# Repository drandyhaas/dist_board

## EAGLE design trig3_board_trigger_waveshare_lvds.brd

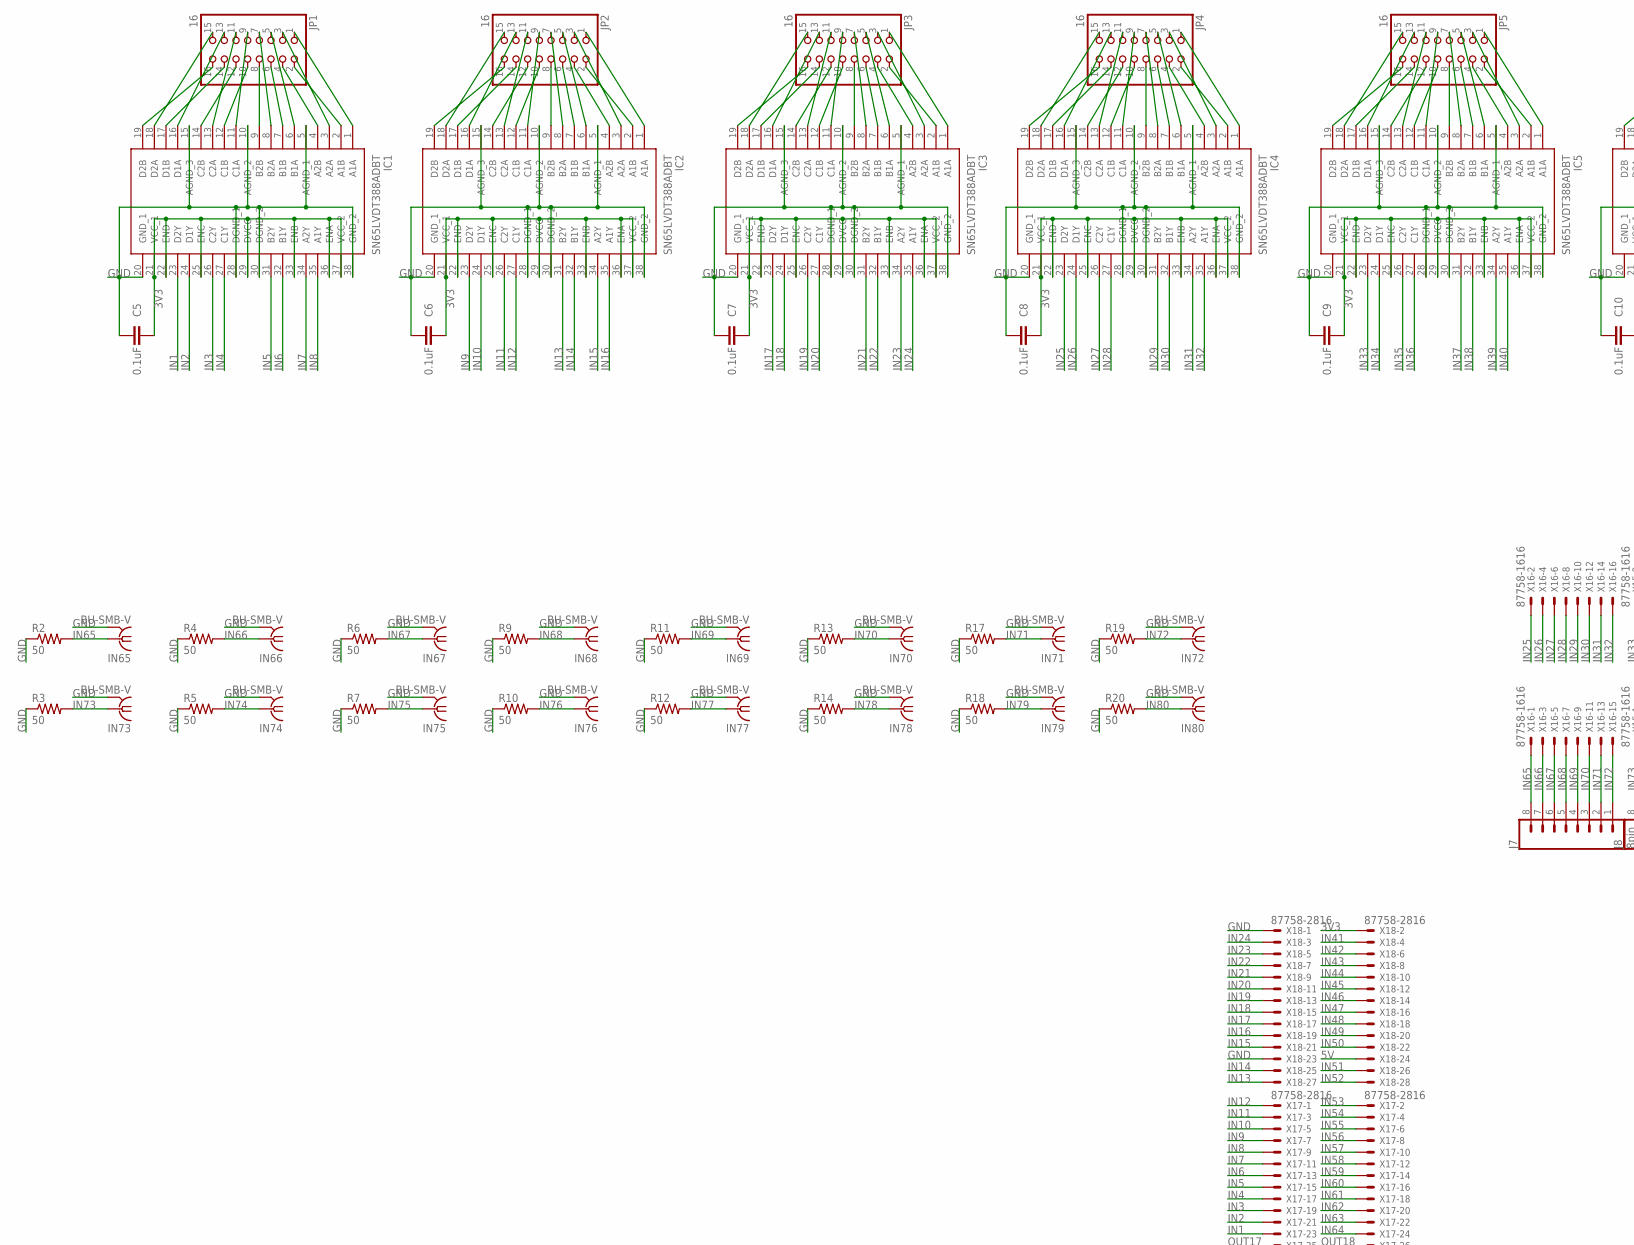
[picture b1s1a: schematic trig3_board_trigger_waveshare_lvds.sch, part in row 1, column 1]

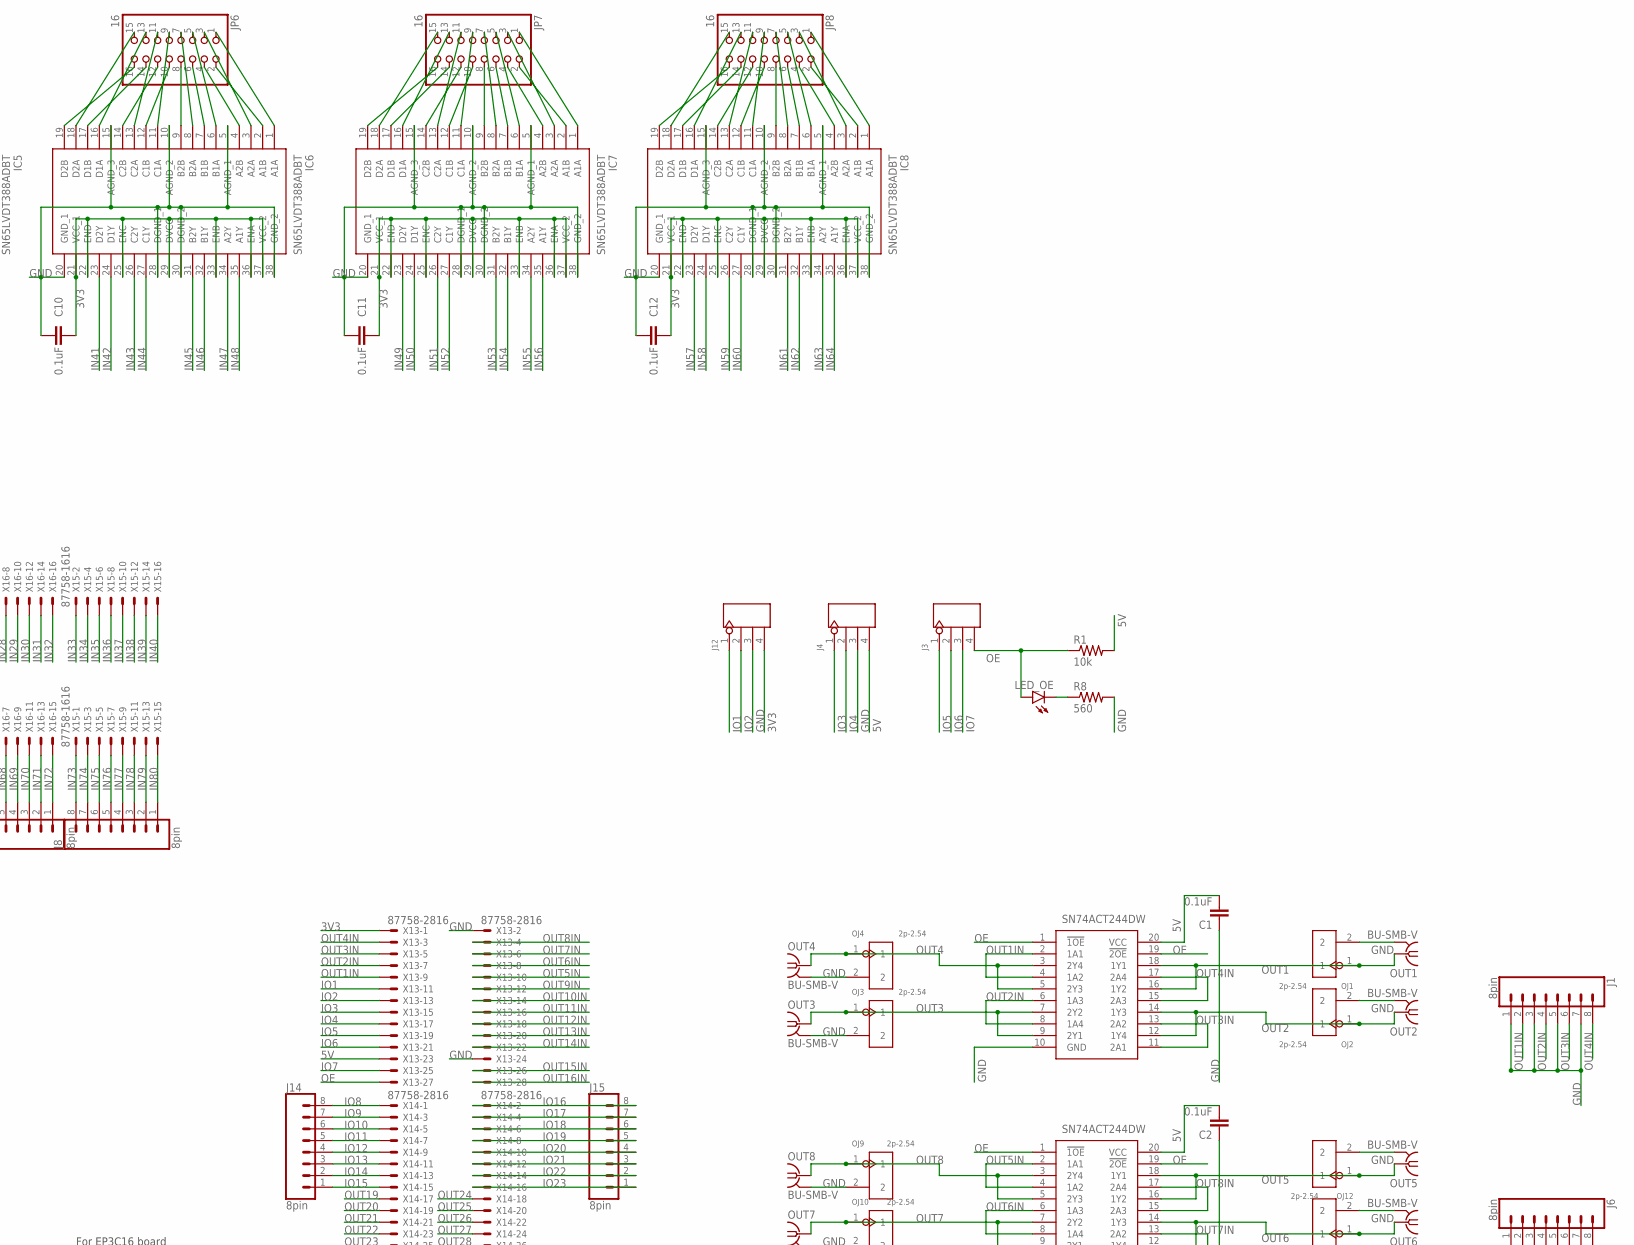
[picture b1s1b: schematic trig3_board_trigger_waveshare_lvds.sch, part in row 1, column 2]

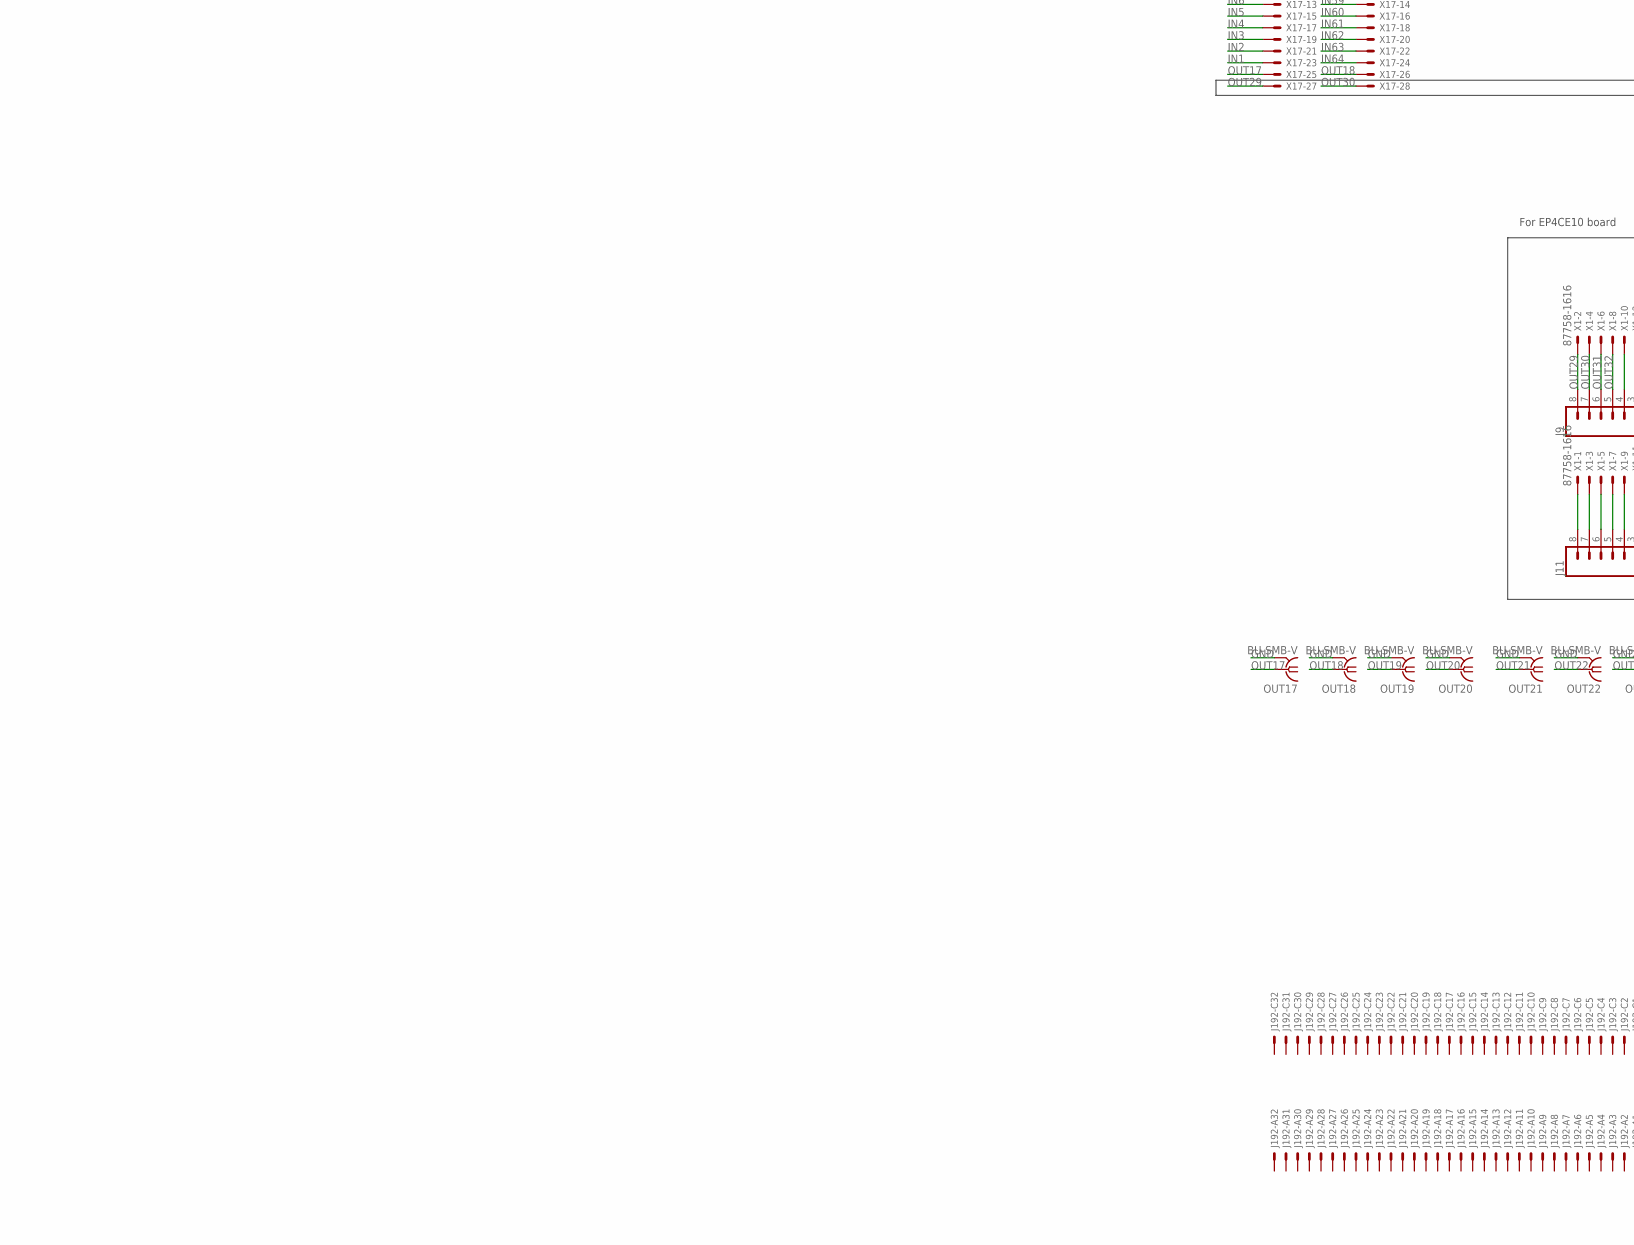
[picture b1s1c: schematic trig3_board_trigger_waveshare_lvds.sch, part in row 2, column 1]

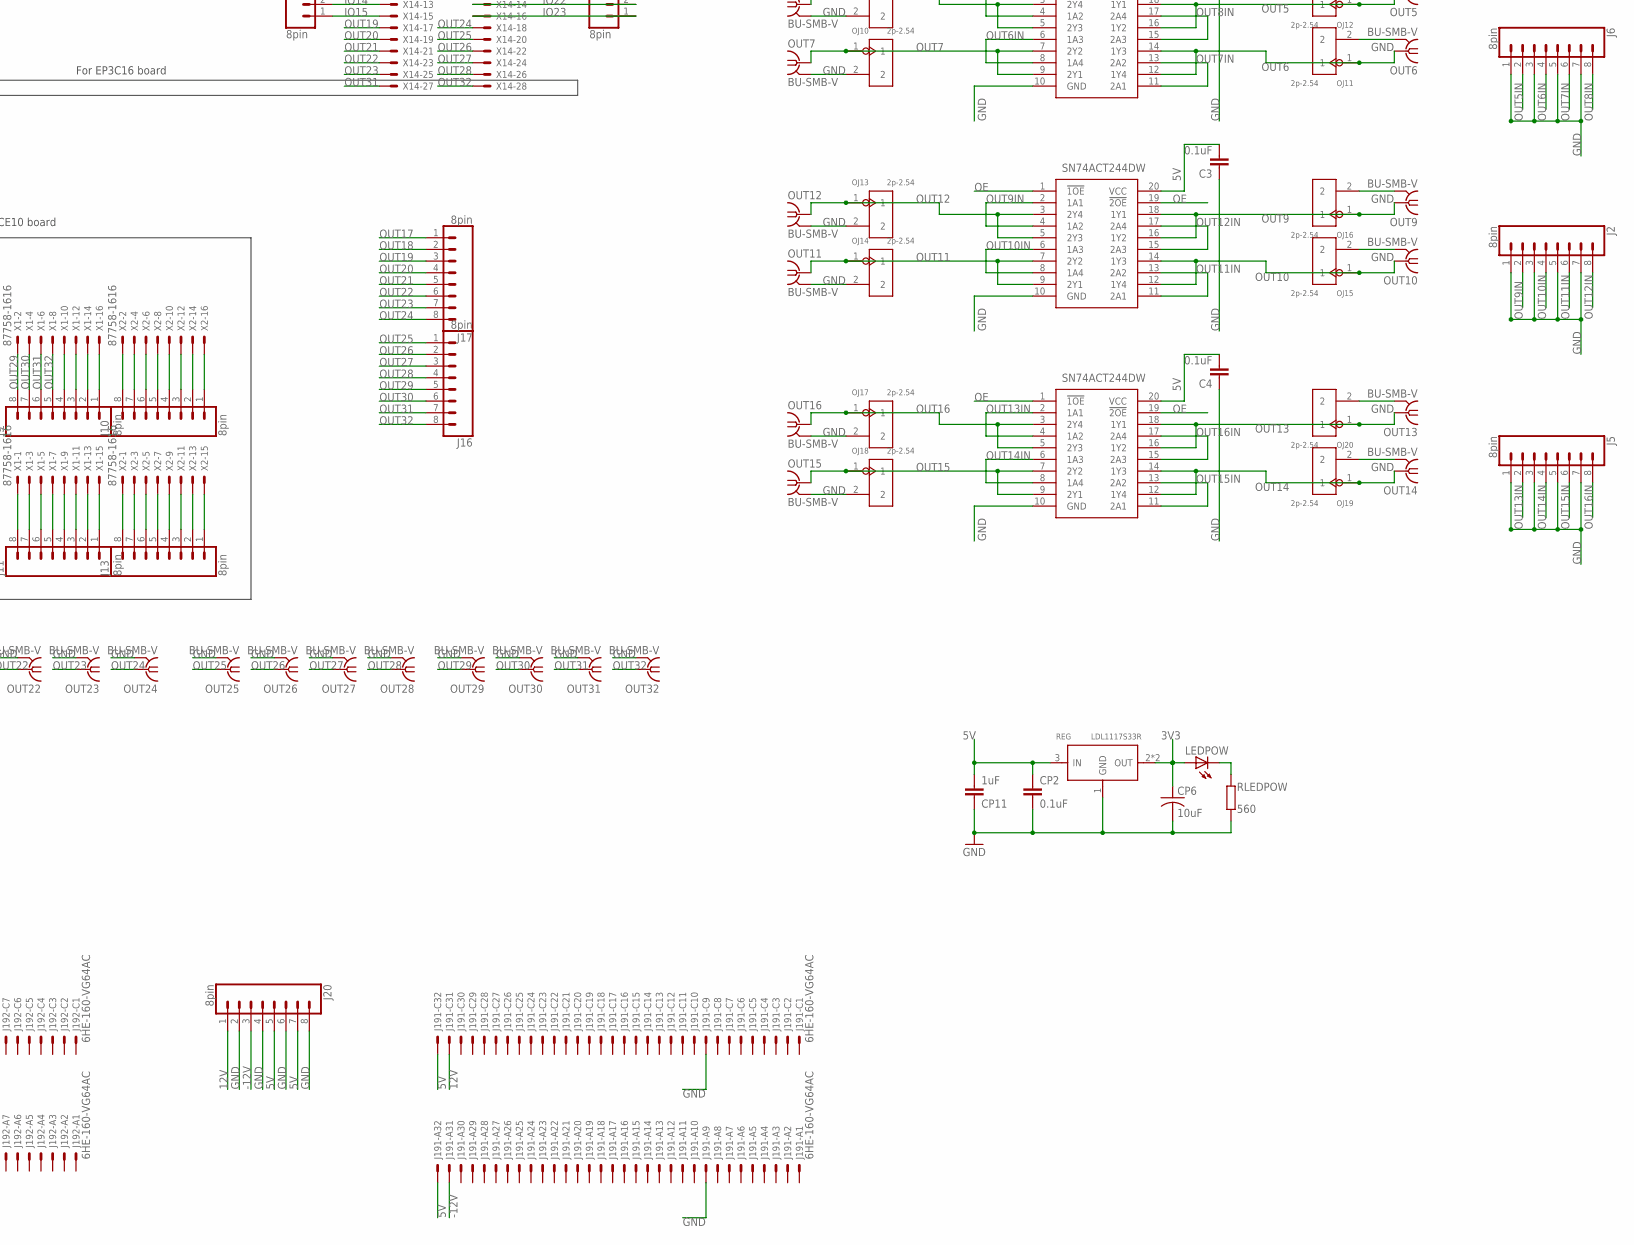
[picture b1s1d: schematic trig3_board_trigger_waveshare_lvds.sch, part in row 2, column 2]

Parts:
C1, C2, C3, C4, C5, C6, C7, C8, C9, C10, C11, C12: 0.1uF; 0805
CP2: 0.1uF; C0805K; MPN MF-CAP-0805-0.1uF
CP6: 10uF; C1206; MPN MF-CAP-1206-10uF
CP11: 1uF; C0805K; MPN MF-CAP-0805-1uF
IC1, IC2, IC3, IC4, IC5, IC6, IC7, IC8: SN65LVDT388ADBT; SOP50P640X120-38N
IN65, IN66, IN67, IN68, IN69, IN70, IN71, IN72, IN73, IN74, IN75, IN76, IN77, IN78, IN79, IN80: BU-SMB-V
J1, J2, J5, J6, J7, J8, J9, J10, J11, J13, J14, J15, J16, J17, J20: 8pin; 1X08
J3, J4, J12: 4p-2.54; H4-2.54
J19: 6HE-160-VG64AC; 6HE_160-VG64AC
JP1, JP2, JP3, JP4, JP5, JP6, JP7, JP8: 16; 2X08/90
LEDPOW: MF-LED-0805-RED; SML0805; MPN MF-LED-0805-RED
LED_OE: OutputEn; CHIP-LED0805
OJ1, OJ2, OJ3, OJ4, OJ9, OJ10, OJ11, OJ12, OJ13, OJ14, OJ15, OJ16, OJ17, OJ18, OJ19, OJ20: 2p-2.54; H2-2.54
OUT1, OUT2, OUT3, OUT4, OUT5, OUT6, OUT7, OUT8, OUT9, OUT10, OUT11, OUT12, OUT13, OUT14, OUT15, OUT16, OUT17, OUT18, OUT19, OUT20, OUT21, OUT22, OUT23, OUT24, OUT25, OUT26, OUT27, OUT28, OUT29, OUT30, OUT31, OUT32: BU-SMB-V
R1: 10k; R0805
R2, R3, R4, R5, R6, R7, R9, R10, R11, R12, R13, R14, R17, R18, R19, R20: 50; AXIAL-0.3
R8: 560; R0805
REG: LDL1117S33R; SOT-223; MPN LDL1117S33R
RLEDPOW: 560; R0805; MPN MF-RES-0805-560
VSLUE, VSLUE2, VSLUE3, VSLUE4: SN74ACT244DW; SOIC127P1030X265-20N
X1, X2, X15, X16: 87758-1616
X13, X14, X17, X18: 87758-2816

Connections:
3V3: C5.2, C6.2, C7.2, C8.2, C9.2, C10.2, C11.2, C12.2, CP6.1, IC1.21 (VCC_1), IC1.22 (END), IC1.25 (ENC), IC1.29 (DVCC), IC1.33 (ENB), IC1.36 (ENA), IC1.37 (VCC_2), IC2.21 (VCC_1), IC2.22 (END), IC2.25 (ENC), IC2.29 (DVCC), IC2.33 (ENB), IC2.36 (ENA), IC2.37 (VCC_2), IC3.21 (VCC_1), IC3.22 (END), IC3.25 (ENC), IC3.29 (DVCC), IC3.33 (ENB), IC3.36 (ENA), IC3.37 (VCC_2), IC4.21 (VCC_1), IC4.22 (END), IC4.25 (ENC), IC4.29 (DVCC), IC4.33 (ENB), IC4.36 (ENA), IC4.37 (VCC_2), IC5.21 (VCC_1), IC5.22 (END), IC5.25 (ENC), IC5.29 (DVCC), IC5.33 (ENB), IC5.36 (ENA), IC5.37 (VCC_2), IC6.21 (VCC_1), IC6.22 (END), IC6.25 (ENC), IC6.29 (DVCC), IC6.33 (ENB), IC6.36 (ENA), IC6.37 (VCC_2), IC7.21 (VCC_1), IC7.22 (END), IC7.25 (ENC), IC7.29 (DVCC), IC7.33 (ENB), IC7.36 (ENA), IC7.37 (VCC_2), IC8.21 (VCC_1), IC8.22 (END), IC8.25 (ENC), IC8.29 (DVCC), IC8.33 (ENB), IC8.36 (ENA), IC8.37 (VCC_2), J12.4, LEDPOW.A, REG.2 (OUT), REG.TER (OUT), X13.1, X18.2
5V: C1.2, C2.2, C3.2, C4.2, CP2.1, CP11.2, J4.4, J19.1-A32 (MS), J19.1-C32 (MS), J20.5, J20.7, R1.2, REG.3 (IN), VSLUE.20 (VCC), VSLUE2.20 (VCC), VSLUE3.20 (VCC), VSLUE4.20 (VCC), X13.23, X18.24
12V: J19.1-C31 (MS), J20.1
-12V: J19.1-A31 (MS), J20.3
GND: C1.1, C2.1, C3.1, C4.1, C5.1, C6.1, C7.1, C8.1, C9.1, C10.1, C11.1, C12.1, CP2.2, CP6.2, CP11.1, IC1.5 (AGND_1), IC1.10 (AGND_2), IC1.15 (AGND_3), IC1.20 (GND_1), IC1.28 (DGND_1), IC1.30 (DGND_2), IC1.38 (GND_2), IC2.5 (AGND_1), IC2.10 (AGND_2), IC2.15 (AGND_3), IC2.20 (GND_1), IC2.28 (DGND_1), IC2.30 (DGND_2), IC2.38 (GND_2), IC3.5 (AGND_1), IC3.10 (AGND_2), IC3.15 (AGND_3), IC3.20 (GND_1), IC3.28 (DGND_1), IC3.30 (DGND_2), IC3.38 (GND_2), IC4.5 (AGND_1), IC4.10 (AGND_2), IC4.15 (AGND_3), IC4.20 (GND_1), IC4.28 (DGND_1), IC4.30 (DGND_2), IC4.38 (GND_2), IC5.5 (AGND_1), IC5.10 (AGND_2), IC5.15 (AGND_3), IC5.20 (GND_1), IC5.28 (DGND_1), IC5.30 (DGND_2), IC5.38 (GND_2), IC6.5 (AGND_1), IC6.10 (AGND_2), IC6.15 (AGND_3), IC6.20 (GND_1), IC6.28 (DGND_1), IC6.30 (DGND_2), IC6.38 (GND_2), IC7.5 (AGND_1), IC7.10 (AGND_2), IC7.15 (AGND_3), IC7.20 (GND_1), IC7.28 (DGND_1), IC7.30 (DGND_2), IC7.38 (GND_2), IC8.5 (AGND_1), IC8.10 (AGND_2), IC8.15 (AGND_3), IC8.20 (GND_1), IC8.28 (DGND_1), IC8.30 (DGND_2), IC8.38 (GND_2), IN65.2, IN65.3 (2), IN65.4 (2), IN65.5 (2), IN66.2, IN66.3 (2), IN66.4 (2), IN66.5 (2), IN67.2, IN67.3 (2), IN67.4 (2), IN67.5 (2), IN68.2, IN68.3 (2), IN68.4 (2), IN68.5 (2), IN69.2, IN69.3 (2), IN69.4 (2), IN69.5 (2), IN70.2, IN70.3 (2), IN70.4 (2), IN70.5 (2), IN71.2, IN71.3 (2), IN71.4 (2), IN71.5 (2), IN72.2, IN72.3 (2), IN72.4 (2), IN72.5 (2), IN73.2, IN73.3 (2), IN73.4 (2), IN73.5 (2), IN74.2, IN74.3 (2), IN74.4 (2), IN74.5 (2), IN75.2, IN75.3 (2), IN75.4 (2), IN75.5 (2), IN76.2, IN76.3 (2), IN76.4 (2), IN76.5 (2), IN77.2, IN77.3 (2), IN77.4 (2), IN77.5 (2), IN78.2, IN78.3 (2), IN78.4 (2), IN78.5 (2), IN79.2, IN79.3 (2), IN79.4 (2), IN79.5 (2), IN80.2, IN80.3 (2), IN80.4 (2), IN80.5 (2), J1.1, J1.3, J1.5, J1.7, J2.1, J2.3, J2.5, J2.7, J4.3, J5.1, J5.3, J5.5, J5.7, J6.1, J6.3, J6.5, J6.7, J12.3, J19.1-A9 (MS), J19.1-C9 (MS), J20.2, J20.4, J20.6, J20.8, OJ1.2, OJ2.2, OJ3.2, OJ4.2, OJ9.2, OJ10.2, OJ11.2, OJ12.2, OJ13.2, OJ14.2, OJ15.2, OJ16.2, OJ17.2, OJ18.2, OJ19.2, OJ20.2, OUT1.2, OUT1.3 (2), OUT1.4 (2), OUT1.5 (2), OUT2.2, OUT2.3 (2), OUT2.4 (2), OUT2.5 (2), OUT3.2, OUT3.3 (2), OUT3.4 (2), OUT3.5 (2), OUT4.2, OUT4.3 (2), OUT4.4 (2), OUT4.5 (2), OUT5.2, OUT5.3 (2), OUT5.4 (2), OUT5.5 (2), OUT6.2, OUT6.3 (2), OUT6.4 (2), OUT6.5 (2), OUT7.2, OUT7.3 (2), OUT7.4 (2), OUT7.5 (2), OUT8.2, OUT8.3 (2), OUT8.4 (2), OUT8.5 (2), OUT9.2, OUT9.3 (2), OUT9.4 (2), OUT9.5 (2), OUT10.2, OUT10.3 (2), OUT10.4 (2), OUT10.5 (2), OUT11.2, OUT11.3 (2), OUT11.4 (2), OUT11.5 (2), OUT12.2, OUT12.3 (2), OUT12.4 (2), OUT12.5 (2), OUT13.2, OUT13.3 (2), OUT13.4 (2), OUT13.5 (2), OUT14.2, OUT14.3 (2), OUT14.4 (2), OUT14.5 (2), OUT15.2, OUT15.3 (2), OUT15.4 (2), OUT15.5 (2), OUT16.2, OUT16.3 (2), OUT16.4 (2), OUT16.5 (2), OUT17.2, OUT17.3 (2), OUT17.4 (2), OUT17.5 (2), OUT18.2, OUT18.3 (2), OUT18.4 (2), OUT18.5 (2), OUT19.2, OUT19.3 (2), OUT19.4 (2), OUT19.5 (2), OUT20.2, OUT20.3 (2), OUT20.4 (2), OUT20.5 (2), OUT21.2, OUT21.3 (2), OUT21.4 (2), OUT21.5 (2), OUT22.2, OUT22.3 (2), OUT22.4 (2), OUT22.5 (2), OUT23.2, OUT23.3 (2), OUT23.4 (2), OUT23.5 (2), OUT24.2, OUT24.3 (2), OUT24.4 (2), OUT24.5 (2), OUT25.2, OUT25.3 (2), OUT25.4 (2), OUT25.5 (2), OUT26.2, OUT26.3 (2), OUT26.4 (2), OUT26.5 (2), OUT27.2, OUT27.3 (2), OUT27.4 (2), OUT27.5 (2), OUT28.2, OUT28.3 (2), OUT28.4 (2), OUT28.5 (2), OUT29.2, OUT29.3 (2), OUT29.4 (2), OUT29.5 (2), OUT30.2, OUT30.3 (2), OUT30.4 (2), OUT30.5 (2), OUT31.2, OUT31.3 (2), OUT31.4 (2), OUT31.5 (2), OUT32.2, OUT32.3 (2), OUT32.4 (2), OUT32.5 (2), R2.P$1 (1), R3.P$1 (1), R4.P$1 (1), R5.P$1 (1), R6.P$1 (1), R7.P$1 (1), R8.2, R9.P$1 (1), R10.P$1 (1), R11.P$1 (1), R12.P$1 (1), R13.P$1 (1), R14.P$1 (1), R17.P$1 (1), R18.P$1 (1), R19.P$1 (1), R20.P$1 (1), REG.1 (GND), RLEDPOW.2, VSLUE.10 (GND), VSLUE2.10 (GND), VSLUE3.10 (GND), VSLUE4.10 (GND), X13.2, X13.24, X18.1, X18.23
IN1: IC1.23 (D2Y), X17.23
IN2: IC1.24 (D1Y), X17.21
IN3: IC1.26 (C2Y), X17.19
IN4: IC1.27 (C1Y), X17.17
IN5: IC1.31 (B2Y), X17.15
IN6: IC1.32 (B1Y), X17.13
IN7: IC1.34 (A2Y), X17.11
IN8: IC1.35 (A1Y), X17.9
IN9: IC2.23 (D2Y), X17.7
IN10: IC2.24 (D1Y), X17.5
IN11: IC2.26 (C2Y), X17.3
IN12: IC2.27 (C1Y), X17.1
IN13: IC2.31 (B2Y), X18.27
IN14: IC2.32 (B1Y), X18.25
IN15: IC2.34 (A2Y), X18.21
IN16: IC2.35 (A1Y), X18.19
IN17: IC3.23 (D2Y), X18.17
IN18: IC3.24 (D1Y), X18.15
IN19: IC3.26 (C2Y), X18.13
IN20: IC3.27 (C1Y), X18.11
IN21: IC3.31 (B2Y), X18.9
IN22: IC3.32 (B1Y), X18.7
IN23: IC3.34 (A2Y), X18.5
IN24: IC3.35 (A1Y), X18.3
IN25: IC4.23 (D2Y), X16.2
IN26: IC4.24 (D1Y), X16.4
IN27: IC4.26 (C2Y), X16.6
IN28: IC4.27 (C1Y), X16.8
IN29: IC4.31 (B2Y), X16.10
IN30: IC4.32 (B1Y), X16.12
IN31: IC4.34 (A2Y), X16.14
IN32: IC4.35 (A1Y), X16.16
IN33: IC5.23 (D2Y), X15.2
IN34: IC5.24 (D1Y), X15.4
IN35: IC5.26 (C2Y), X15.6
IN36: IC5.27 (C1Y), X15.8
IN37: IC5.31 (B2Y), X15.10
IN38: IC5.32 (B1Y), X15.12
IN39: IC5.34 (A2Y), X15.14
IN40: IC5.35 (A1Y), X15.16
IN41: IC6.23 (D2Y), X18.4
IN42: IC6.24 (D1Y), X18.6
IN43: IC6.26 (C2Y), X18.8
IN44: IC6.27 (C1Y), X18.10
IN45: IC6.31 (B2Y), X18.12
IN46: IC6.32 (B1Y), X18.14
IN47: IC6.34 (A2Y), X18.16
IN48: IC6.35 (A1Y), X18.18
IN49: IC7.23 (D2Y), X18.20
IN50: IC7.24 (D1Y), X18.22
IN51: IC7.26 (C2Y), X18.26
IN52: IC7.27 (C1Y), X18.28
IN53: IC7.31 (B2Y), X17.2
IN54: IC7.32 (B1Y), X17.4
IN55: IC7.34 (A2Y), X17.6
IN56: IC7.35 (A1Y), X17.8
IN57: IC8.23 (D2Y), X17.10
IN58: IC8.24 (D1Y), X17.12
IN59: IC8.26 (C2Y), X17.14
IN60: IC8.27 (C1Y), X17.16
IN61: IC8.31 (B2Y), X17.18
IN62: IC8.32 (B1Y), X17.20
IN63: IC8.34 (A2Y), X17.22
IN64: IC8.35 (A1Y), X17.24
IN65: IN65.1, J7.8, R2.P$2 (2), X16.1
IN66: IN66.1, J7.7, R4.P$2 (2), X16.3
IN67: IN67.1, J7.6, R6.P$2 (2), X16.5
IN68: IN68.1, J7.5, R9.P$2 (2), X16.7
IN69: IN69.1, J7.4, R11.P$2 (2), X16.9
IN70: IN70.1, J7.3, R13.P$2 (2), X16.11
IN71: IN71.1, J7.2, R17.P$2 (2), X16.13
IN72: IN72.1, J7.1, R19.P$2 (2), X16.15
IN73: IN73.1, J8.8, R3.P$2 (2), X15.1
IN74: IN74.1, J8.7, R5.P$2 (2), X15.3
IN75: IN75.1, J8.6, R7.P$2 (2), X15.5
IN76: IN76.1, J8.5, R10.P$2 (2), X15.7
IN77: IN77.1, J8.4, R12.P$2 (2), X15.9
IN78: IN78.1, J8.3, R14.P$2 (2), X15.11
IN79: IN79.1, J8.2, R18.P$2 (2), X15.13
IN80: IN80.1, J8.1, R20.P$2 (2), X15.15
IO1: J12.1, X13.11
IO2: J12.2, X13.13
IO3: J4.1, X13.15
IO4: J4.2, X13.17
IO5: J3.1, X13.19
IO6: J3.2, X13.21
IO7: J3.3, X13.25
IO8: J14.8, X14.1
IO9: J14.7, X14.3
IO10: J14.6, X14.5
IO11: J14.5, X14.7
IO12: J14.4, X14.9
IO13: J14.3, X14.11
IO14: J14.2, X14.13
IO15: J14.1, X14.15
IO16: J15.8, X14.2
IO17: J15.7, X14.4
IO18: J15.6, X14.6
IO19: J15.5, X14.8
IO20: J15.4, X14.10
IO21: J15.3, X14.12
IO22: J15.2, X14.14
IO23: J15.1, X14.16
unnamed: IC2.1 (A1A), JP2.1
unnamed: IC2.2 (A1B), JP2.2
unnamed: IC2.3 (A2A), JP2.3
unnamed: IC2.4 (A2B), JP2.4
unnamed: IC2.6 (B1A), JP2.5
unnamed: IC2.7 (B1B), JP2.6
unnamed: IC2.8 (B2A), JP2.7
unnamed: IC2.9 (B2B), JP2.8
unnamed: IC1.1 (A1A), JP1.1
unnamed: IC1.2 (A1B), JP1.2
unnamed: IC1.3 (A2A), JP1.3
unnamed: IC1.4 (A2B), JP1.4
unnamed: IC1.6 (B1A), JP1.5
unnamed: IC1.7 (B1B), JP1.6
unnamed: IC1.8 (B2A), JP1.7
unnamed: IC1.9 (B2B), JP1.8
unnamed: IC1.11 (C1A), JP1.9
unnamed: IC1.12 (C1B), JP1.10
unnamed: IC1.13 (C2A), JP1.11
unnamed: IC1.14 (C2B), JP1.12
unnamed: IC1.16 (D1A), JP1.13
unnamed: IC1.17 (D1B), JP1.14
unnamed: IC1.18 (D2A), JP1.15
unnamed: IC1.19 (D2B), JP1.16
unnamed: IC2.11 (C1A), JP2.9
unnamed: IC2.12 (C1B), JP2.10
unnamed: IC2.13 (C2A), JP2.11
unnamed: IC2.14 (C2B), JP2.12
unnamed: IC2.16 (D1A), JP2.13
unnamed: IC2.17 (D1B), JP2.14
unnamed: IC2.18 (D2A), JP2.15
unnamed: IC2.19 (D2B), JP2.16
unnamed: IC3.1 (A1A), JP3.1
unnamed: IC3.2 (A1B), JP3.2
unnamed: IC3.3 (A2A), JP3.3
unnamed: LEDPOW.C, RLEDPOW.1
unnamed: IC3.4 (A2B), JP3.4
unnamed: IC3.6 (B1A), JP3.5
unnamed: IC3.7 (B1B), JP3.6
unnamed: IC3.8 (B2A), JP3.7
unnamed: IC3.9 (B2B), JP3.8
unnamed: IC3.11 (C1A), JP3.9
unnamed: IC3.12 (C1B), JP3.10
unnamed: IC3.13 (C2A), JP3.11
unnamed: IC3.14 (C2B), JP3.12
unnamed: IC3.16 (D1A), JP3.13
unnamed: IC3.17 (D1B), JP3.14
unnamed: IC3.18 (D2A), JP3.15
unnamed: IC3.19 (D2B), JP3.16
unnamed: IC4.1 (A1A), JP4.1
unnamed: IC4.2 (A1B), JP4.2
unnamed: IC4.3 (A2A), JP4.3
unnamed: IC4.4 (A2B), JP4.4
unnamed: IC4.6 (B1A), JP4.5
unnamed: IC4.7 (B1B), JP4.6
unnamed: IC4.8 (B2A), JP4.7
unnamed: IC4.9 (B2B), JP4.8
unnamed: IC4.11 (C1A), JP4.9
unnamed: IC4.12 (C1B), JP4.10
unnamed: IC4.13 (C2A), JP4.11
unnamed: IC4.14 (C2B), JP4.12
unnamed: IC4.16 (D1A), JP4.13
unnamed: IC4.17 (D1B), JP4.14
unnamed: IC4.18 (D2A), JP4.15
unnamed: IC4.19 (D2B), JP4.16
unnamed: IC5.1 (A1A), JP5.1
unnamed: IC5.2 (A1B), JP5.2
unnamed: IC5.3 (A2A), JP5.3
unnamed: IC5.4 (A2B), JP5.4
unnamed: IC5.6 (B1A), JP5.5
unnamed: IC5.7 (B1B), JP5.6
unnamed: IC5.8 (B2A), JP5.7
unnamed: IC5.9 (B2B), JP5.8
unnamed: IC5.11 (C1A), JP5.9
unnamed: IC5.12 (C1B), JP5.10
unnamed: IC5.13 (C2A), JP5.11
unnamed: IC5.14 (C2B), JP5.12
unnamed: IC5.16 (D1A), JP5.13
unnamed: IC5.17 (D1B), JP5.14
unnamed: IC5.18 (D2A), JP5.15
unnamed: IC5.19 (D2B), JP5.16
unnamed: IC6.1 (A1A), JP6.1
unnamed: IC6.2 (A1B), JP6.2
unnamed: IC6.3 (A2A), JP6.3
unnamed: IC6.4 (A2B), JP6.4
unnamed: IC6.6 (B1A), JP6.5
unnamed: IC6.7 (B1B), JP6.6
unnamed: IC6.8 (B2A), JP6.7
unnamed: IC6.9 (B2B), JP6.8
unnamed: IC6.11 (C1A), JP6.9
unnamed: IC6.12 (C1B), JP6.10
unnamed: IC6.13 (C2A), JP6.11
unnamed: IC6.14 (C2B), JP6.12
unnamed: IC6.16 (D1A), JP6.13
unnamed: IC6.17 (D1B), JP6.14
unnamed: IC6.18 (D2A), JP6.15
unnamed: IC6.19 (D2B), JP6.16
unnamed: IC7.1 (A1A), JP7.1
unnamed: IC7.2 (A1B), JP7.2
unnamed: IC7.3 (A2A), JP7.3
unnamed: IC7.4 (A2B), JP7.4
unnamed: IC7.6 (B1A), JP7.5
unnamed: IC7.7 (B1B), JP7.6
unnamed: IC7.8 (B2A), JP7.7
unnamed: IC7.9 (B2B), JP7.8
unnamed: IC7.11 (C1A), JP7.9
unnamed: IC7.12 (C1B), JP7.10
unnamed: IC7.13 (C2A), JP7.11
unnamed: IC7.14 (C2B), JP7.12
unnamed: IC7.16 (D1A), JP7.13
unnamed: IC7.17 (D1B), JP7.14
unnamed: IC7.18 (D2A), JP7.15
unnamed: IC7.19 (D2B), JP7.16
unnamed: IC8.1 (A1A), JP8.1
unnamed: IC8.2 (A1B), JP8.2
unnamed: IC8.3 (A2A), JP8.3
unnamed: IC8.4 (A2B), JP8.4
unnamed: IC8.6 (B1A), JP8.5
unnamed: IC8.7 (B1B), JP8.6
unnamed: IC8.8 (B2A), JP8.7
unnamed: IC8.9 (B2B), JP8.8
unnamed: IC8.11 (C1A), JP8.9
unnamed: IC8.12 (C1B), JP8.10
unnamed: IC8.13 (C2A), JP8.11
unnamed: IC8.14 (C2B), JP8.12
unnamed: IC8.16 (D1A), JP8.13
unnamed: IC8.17 (D1B), JP8.14
unnamed: IC8.18 (D2A), JP8.15
unnamed: IC8.19 (D2B), JP8.16
unnamed: LED_OE.C, R8.1
unnamed: J9.4, X1.10
unnamed: J9.3, X1.12
unnamed: J9.2, X1.14
unnamed: J9.1, X1.16
unnamed: J10.8, X2.2
unnamed: J10.7, X2.4
unnamed: J10.6, X2.6
unnamed: J10.5, X2.8
unnamed: J10.4, X2.10
unnamed: J10.3, X2.12
unnamed: J10.2, X2.14
unnamed: J10.1, X2.16
unnamed: J11.8, X1.1
unnamed: J11.7, X1.3
unnamed: J11.6, X1.5
unnamed: J11.5, X1.7
unnamed: J11.4, X1.9
unnamed: J11.3, X1.11
unnamed: J11.2, X1.13
unnamed: J11.1, X1.15
unnamed: J13.8, X2.1
unnamed: J13.7, X2.3
unnamed: J13.6, X2.5
unnamed: J13.5, X2.7
unnamed: J13.4, X2.9
unnamed: J13.3, X2.11
unnamed: J13.2, X2.13
unnamed: J13.1, X2.15
OE: J3.4, LED_OE.A, R1.1, VSLUE.1 (!1OE), VSLUE.19 (!2OE), VSLUE2.1 (!1OE), VSLUE2.19 (!2OE), VSLUE3.1 (!1OE), VSLUE3.19 (!2OE), VSLUE4.1 (!1OE), VSLUE4.19 (!2OE), X13.27
OUT1: OJ1.1, OUT1.1, VSLUE.16 (1Y2), VSLUE.18 (1Y1)
OUT1IN: J1.2, VSLUE.2 (1A1), VSLUE.4 (1A2), X13.9
OUT2: OJ2.1, OUT2.1, VSLUE.12 (1Y4), VSLUE.14 (1Y3)
OUT2IN: J1.4, VSLUE.6 (1A3), VSLUE.8 (1A4), X13.7
OUT3: OJ3.1, OUT3.1, VSLUE.7 (2Y2), VSLUE.9 (2Y1)
OUT3IN: J1.6, VSLUE.11 (2A1), VSLUE.13 (2A2), X13.5
OUT4: OJ4.1, OUT4.1, VSLUE.3 (2Y4), VSLUE.5 (2Y3)
OUT4IN: J1.8, VSLUE.15 (2A3), VSLUE.17 (2A4), X13.3
OUT5: OJ12.1, OUT5.1, VSLUE2.16 (1Y2), VSLUE2.18 (1Y1)
OUT5IN: J6.2, VSLUE2.2 (1A1), VSLUE2.4 (1A2), X13.10
OUT6: OJ11.1, OUT6.1, VSLUE2.12 (1Y4), VSLUE2.14 (1Y3)
OUT6IN: J6.4, VSLUE2.6 (1A3), VSLUE2.8 (1A4), X13.8
OUT7: OJ10.1, OUT7.1, VSLUE2.7 (2Y2), VSLUE2.9 (2Y1)
OUT7IN: J6.6, VSLUE2.11 (2A1), VSLUE2.13 (2A2), X13.6
OUT8: OJ9.1, OUT8.1, VSLUE2.3 (2Y4), VSLUE2.5 (2Y3)
OUT8IN: J6.8, VSLUE2.15 (2A3), VSLUE2.17 (2A4), X13.4
OUT9: OJ16.1, OUT9.1, VSLUE3.16 (1Y2), VSLUE3.18 (1Y1)
OUT9IN: J2.2, VSLUE3.2 (1A1), VSLUE3.4 (1A2), X13.12
OUT10: OJ15.1, OUT10.1, VSLUE3.12 (1Y4), VSLUE3.14 (1Y3)
OUT10IN: J2.4, VSLUE3.6 (1A3), VSLUE3.8 (1A4), X13.14
OUT11: OJ14.1, OUT11.1, VSLUE3.7 (2Y2), VSLUE3.9 (2Y1)
OUT11IN: J2.6, VSLUE3.11 (2A1), VSLUE3.13 (2A2), X13.16
OUT12: OJ13.1, OUT12.1, VSLUE3.3 (2Y4), VSLUE3.5 (2Y3)
OUT12IN: J2.8, VSLUE3.15 (2A3), VSLUE3.17 (2A4), X13.18
OUT13: OJ20.1, OUT13.1, VSLUE4.16 (1Y2), VSLUE4.18 (1Y1)
OUT13IN: J5.2, VSLUE4.2 (1A1), VSLUE4.4 (1A2), X13.20
OUT14: OJ19.1, OUT14.1, VSLUE4.12 (1Y4), VSLUE4.14 (1Y3)
OUT14IN: J5.4, VSLUE4.6 (1A3), VSLUE4.8 (1A4), X13.22
OUT15: OJ18.1, OUT15.1, VSLUE4.7 (2Y2), VSLUE4.9 (2Y1)
OUT15IN: J5.6, VSLUE4.11 (2A1), VSLUE4.13 (2A2), X13.26
OUT16: OJ17.1, OUT16.1, VSLUE4.3 (2Y4), VSLUE4.5 (2Y3)
OUT16IN: J5.8, VSLUE4.15 (2A3), VSLUE4.17 (2A4), X13.28
OUT17: J17.1, OUT17.1, X17.25
OUT18: J17.2, OUT18.1, X17.26
OUT19: J17.3, OUT19.1, X14.17
OUT20: J17.4, OUT20.1, X14.19
OUT21: J17.5, OUT21.1, X14.21
OUT22: J17.6, OUT22.1, X14.23
OUT23: J17.7, OUT23.1, X14.25
OUT24: J17.8, OUT24.1, X14.18
OUT25: J16.1, OUT25.1, X14.20
OUT26: J16.2, OUT26.1, X14.22
OUT27: J16.3, OUT27.1, X14.24
OUT28: J16.4, OUT28.1, X14.26
OUT29: J9.8, J16.5, OUT29.1, X1.2, X17.27
OUT30: J9.7, J16.6, OUT30.1, X1.4, X17.28
OUT31: J9.6, J16.7, OUT31.1, X1.6, X14.27
OUT32: J9.5, J16.8, OUT32.1, X1.8, X14.28

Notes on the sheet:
For EP4CE10 board
For EP3C16 board

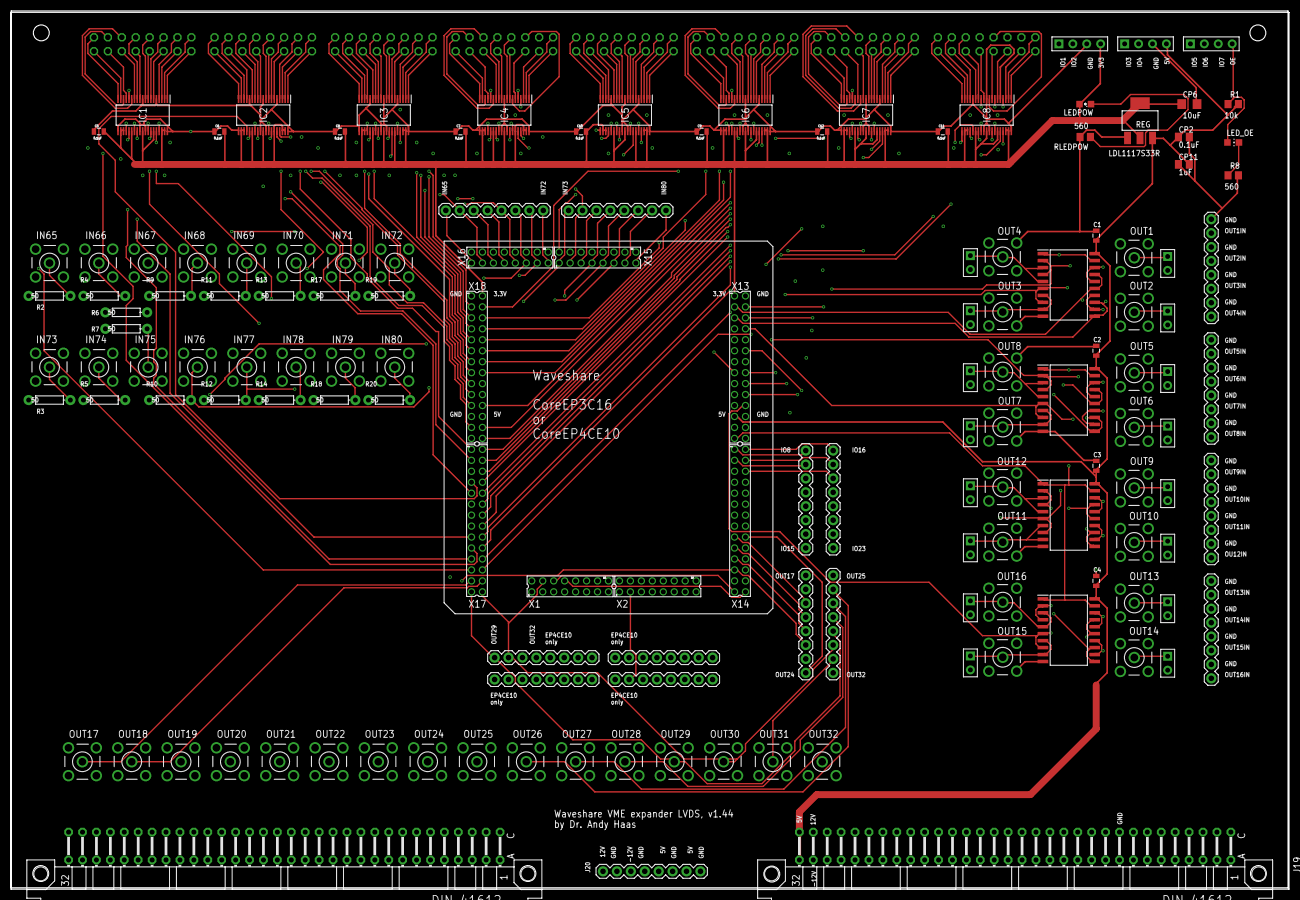
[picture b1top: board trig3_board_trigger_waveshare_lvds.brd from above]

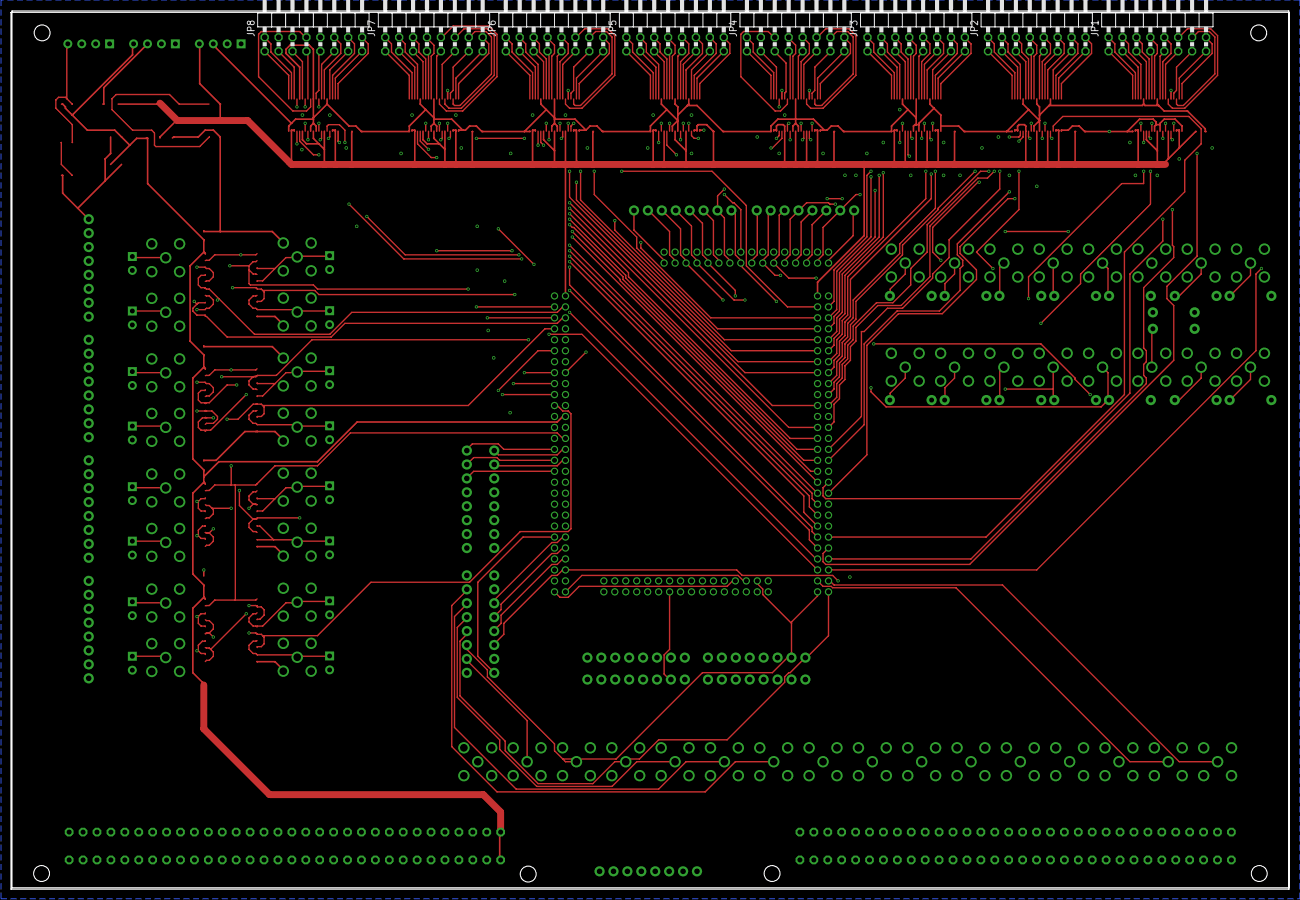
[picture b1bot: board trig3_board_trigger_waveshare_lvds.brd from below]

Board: 4 copper layers, 233.2 x 160.0 mm, 148 parts (8 on the bottom side), 315 nets.

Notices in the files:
parts and their libraries:
SparkFun-Passives: Licensing: Creative Commons ShareAlike 4.0 International - https://creativecommons.org/licenses/by-sa/4.0
